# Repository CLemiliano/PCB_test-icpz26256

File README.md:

# PCB_test-icpz26256

Pcb used for testing the optical encoder ic-pz26256 from iC-Haus.

Link to the ic-pz series : https://www.ichaus.de/product/ic-pz-series/#documents

See master branch for kicad files.

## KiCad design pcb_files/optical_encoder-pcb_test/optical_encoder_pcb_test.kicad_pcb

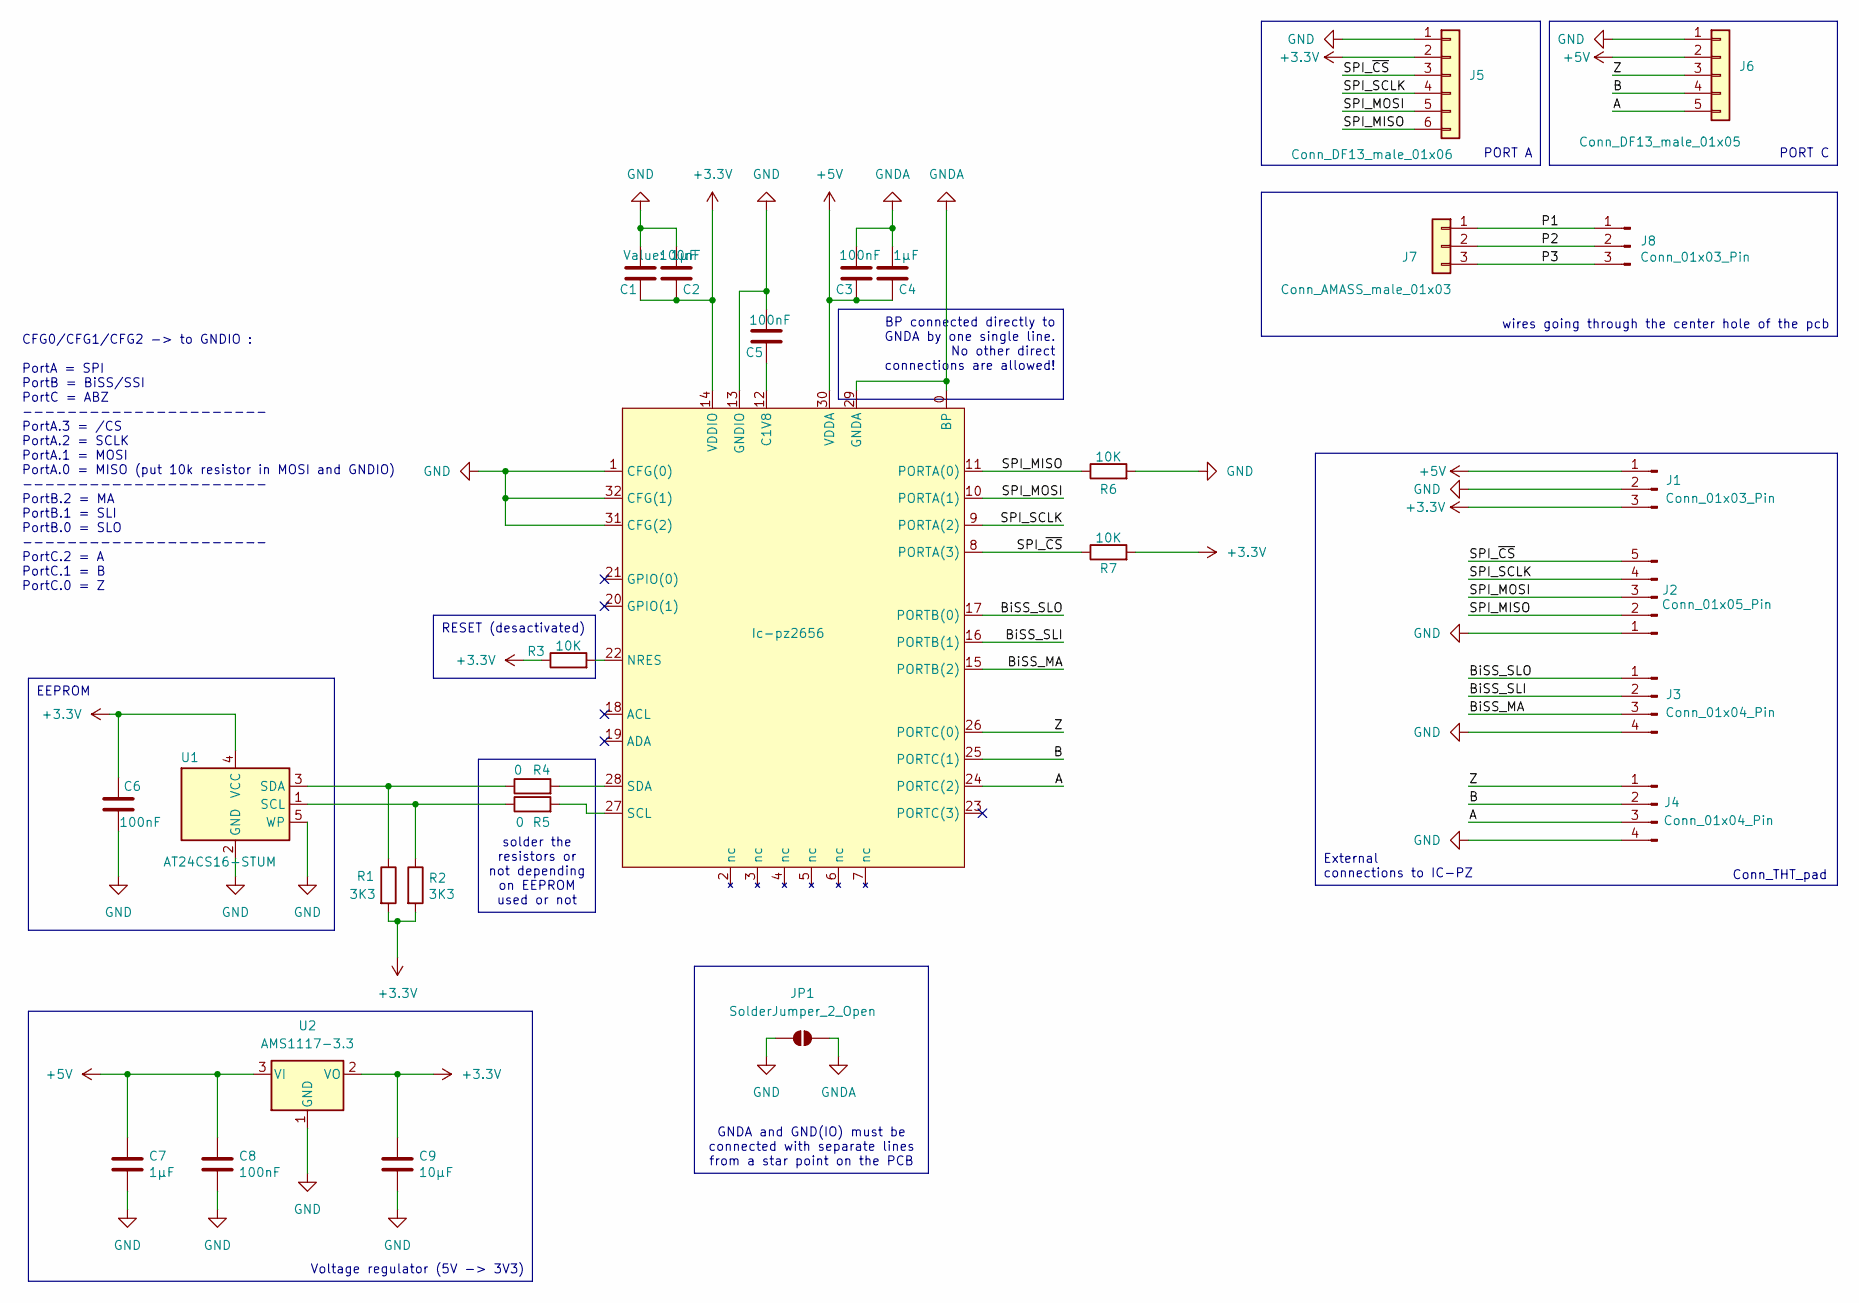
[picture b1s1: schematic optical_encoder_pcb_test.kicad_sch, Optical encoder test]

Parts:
C1, C4: 1μF; C_0603_1608Metric_Pad1.08x0.95mm_HandSolder
C2, C3, C5, C6: 100nF; C_0603_1608Metric_Pad1.08x0.95mm_HandSolder
C7: 1μF; C_0603_1608Metric_Pad1.08x0.95mm_HandSolder; Rated Voltage 10V; Part No GRM033C81A105ME05D; DigiKey 490-13219-1-ND
C8: 100nF; C_0603_1608Metric_Pad1.08x0.95mm_HandSolder; Rated Voltage 10V; Part No GRM033R61E104KE14J; DigiKey 490-14571-1-ND
C9: 10μF; C_0603_1608Metric_Pad1.08x0.95mm_HandSolder; Rated Voltage 10V; Part No GRM188R61A106ME69D; DigiKey 490-10475-1-ND
Ic-pz2656: Ic-pz2656-5x5
J1: Conn_01x03_Pin; PinHeader_1x03_P2.54mm_Vertical
J2: Conn_01x05_Pin; PinHeader_1x05_P2.54mm_Vertical
J3, J4: Conn_01x04_Pin; PinHeader_1x04_P2.54mm_Vertical
J5: Conn_DF13_male_01x06; Hirose_DF13-06P-1.25DSA_1x06_P1.25mm_Vertical
J6: Conn_DF13_male_01x05; Hirose_DF13-05P-1.25DSA_1x05_P1.25mm_Vertical
J7: Conn_AMASS_male_01x03; AMASS_MR30PW-M_1x03_P3.50mm_Horizontal
J8: Conn_01x03_Pin; SolderWire-1.5sqmm_1x03_P6mm_D1.7mm_OD3mm
JP1: SolderJumper_2_Open; SolderJumper-2_P1.3mm_Bridged2Bar_Pad1.0x1.5mm
R1, R2: 3K3; R_0603_1608Metric_Pad0.98x0.95mm_HandSolder
R3, R6, R7: 10K; R_0603_1608Metric_Pad0.98x0.95mm_HandSolder
R4, R5: 0; R_0603_1608Metric_Pad0.98x0.95mm_HandSolder
U1: AT24CS16-STUM; SOT-23-5
U2: AMS1117-3.3; SOT-223-3_TabPin2

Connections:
+3.3V: C1.2, C2.2, C6.2, C9.1, Ic-pz2656.14 (VDDIO), J1.3, J5.2, R1.2, R2.2, R3.1, R7.2, U1.4 (VCC), U2.2 (VO)
+5V: C3.2, C4.2, C7.1, C8.1, Ic-pz2656.30 (VDDA), J1.1, J6.2, U2.3 (VI)
/A: Ic-pz2656.24 (PORTC(2)), J4.3, J6.5
/B: Ic-pz2656.25 (PORTC(1)), J4.2, J6.4
/BiSS_MA: Ic-pz2656.15 (PORTB(2)), J3.3
/BiSS_SLI: Ic-pz2656.16 (PORTB(1)), J3.2
/BiSS_SLO: Ic-pz2656.17 (PORTB(0)), J3.1
/P1: J7.1, J8.1
/P2: J7.2, J8.2
/P3: J7.3, J8.3
/SPI_MISO: Ic-pz2656.11 (PORTA(0)), J2.2, J5.6, R6.1
/SPI_MOSI: Ic-pz2656.10 (PORTA(1)), J2.3, J5.5
/SPI_SCLK: Ic-pz2656.9 (PORTA(2)), J2.4, J5.4
/SPI_~CS: Ic-pz2656.8 (PORTA(3)), J2.5, J5.3, R7.1
/Z: Ic-pz2656.26 (PORTC(0)), J4.1, J6.3
GND: C1.1, C2.1, C5.1, C6.1, C7.2, C8.2, C9.2, Ic-pz2656.1 (CFG(0)), Ic-pz2656.13 (GNDIO), Ic-pz2656.31 (CFG(2)), Ic-pz2656.32 (CFG(1)), J1.2, J2.1, J3.4, J4.4, J5.1, J6.1, JP1.1 (A), R6.2, U1.2 (GND), U1.5 (WP), U2.1 (GND)
GNDA: C3.1, C4.1, Ic-pz2656.0 (BP), Ic-pz2656.29 (GNDA), JP1.2 (B)
unnamed: C5.2, Ic-pz2656.12 (C1V8)
unnamed: Ic-pz2656.22 (NRES), R3.2
unnamed: Ic-pz2656.27 (SCL), R5.2
unnamed: Ic-pz2656.28 (SDA), R4.2
unnamed: R2.1, R5.1, U1.1 (SCL)
unnamed: R1.1, R4.1, U1.3 (SDA)

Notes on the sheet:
PORT C
RESET (desactivated)
Voltage regulator (5V -> 3V3)
External connections to IC-PZ
PORT A
wires going through the center hole of the pcb
GNDA and GND(IO) must be connected with separate lines from a star point on the PCB
solder the resistors or not depending on EEPROM used or not
BP connected directly to GNDA by one single line. No other direct connections are allowed!
EEPROM
Conn_THT_pad
CFG0/CFG1/CFG2 -> to GNDIO : PortA = SPI PortB = BiSS/SSI PortC = ABZ ---------------------- PortA.3 = /CS PortA.2 = SCLK PortA.1 = MOSI PortA.0 = MISO (put 10k resistor in MOSI and GNDIO) ---------------------- PortB.2 = MA PortB.1 = SLI PortB.0 = SLO ---------------------- PortC.2 = A PortC.1 = B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

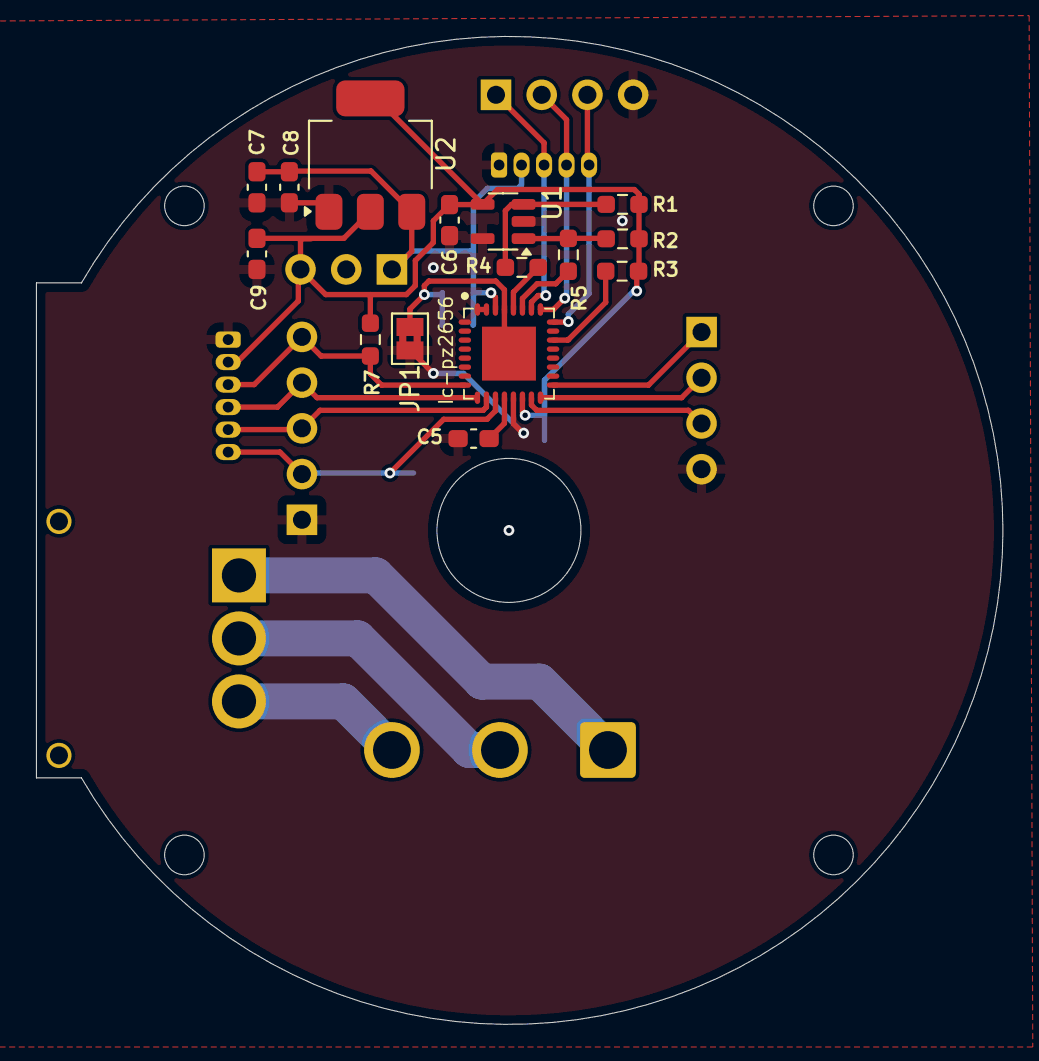
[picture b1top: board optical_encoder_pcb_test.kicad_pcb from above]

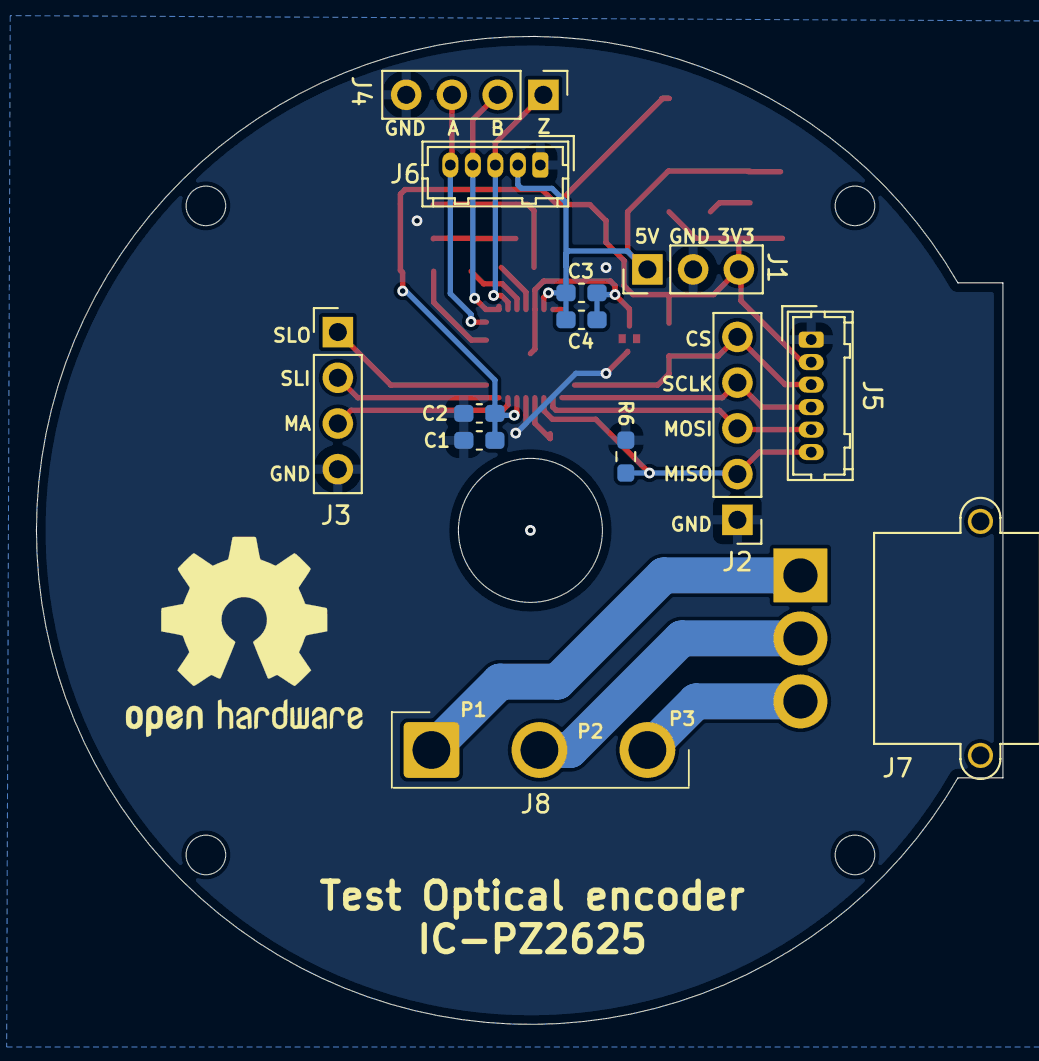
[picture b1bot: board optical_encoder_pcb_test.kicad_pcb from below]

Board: 2 copper layers, 53.7 x 54.9 mm, 28 parts (12 on the bottom side), 23 nets.

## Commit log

2024-05-02 initial project version
2024-05-03 Propositions de corrections v2.
2024-05-13 Story 2 : add voltage regulator, fix configuration, modify connectors
2024-05-14 layout reorganized, add jumper, cahnge layers size, change size of the components footprints
2024-05-23 Double phase traces, C7-C8-C9 switched to front face, C5-R3 moved
2024-05-23 phases planes bug fixed
2024-05-30 unconnected track removed
2024-06-21 connexion issues fixed, ibon file added
2024-06-21 mounting holes replaced
